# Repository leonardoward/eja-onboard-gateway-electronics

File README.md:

# EJA Onboard Gateway - Electronic Design

EJA Onboard Gateway - Electronic Design - [2020 Hackaday Dream Team Challenge for Conservation X Labs](https://hackaday.io/project/173457-2020-hdp-dream-team-conservation-x-labs)

Onboard Gateway is a 134.11 mm x 62.48 mm PCB that integrates the 3 main components (ESP32, LoRa and USB LiIon/LiPoly charger)

This repository contains the KiCad design for the PCB of the Onboard Gateway. It also contains the 3D models used to visualize the design in the KiCad 3D viewer.

## Main Components ##

Sources:

- [ESP32-DEVKITC-32D](https://www.digikey.com/product-detail/es/espressif-systems/ESP32-DEVKITC-32D/1965-1000-ND/9356990)
- [RFM95W LoRa Radio](https://www.digikey.com/product-detail/es/adafruit-industries-llc/3072/1528-1667-ND/6005357)
- [USB LiIon/LiPoly charger](https://www.adafruit.com/product/259)

## Schematic ##

[For a detailed explanation of the schematic visit the following log.](https://hackaday.io/project/173457/log/181839-onboard-gateway-v10-schematic-and-pcb-design)

## PCB Layout ##

## Assembly ##

Components List:

1. [TERM BLK 2P SIDE ENT 5.08MM PCB](https://www.digikey.com/product-detail/es/on-shore-technology-inc/OSTTC022162/ED2609-ND/614558)
2. [CONN HEADER R/A 2POS 2.5MM](https://www.digikey.com/product-detail/es/jst-sales-america-inc/S2B-XH-A-1-LF-SN/455-4226-ND/9961922)
3. [CONN HEADER VERT 2POS 2.54MM](https://www.digikey.com/product-detail/es/3m/2340-6111TG/3M11928-ND/1237275)
4. [CONN HEADER VERT 2POS 2.54MM](https://www.digikey.com/product-detail/es/3m/2340-6111TG/3M11928-ND/1237275)
5. [CONN HDR 6POS 0.1 TIN PCB](https://www.digikey.com/product-detail/es/sullins-connector-solutions/PPTC061LFBN-RC/S7004-ND/810145)
6. 2POS JST cable (included in the [USB LiIon/LiPoly charger](https://www.adafruit.com/product/259))
7. [USB LiIon/LiPoly charger](https://www.adafruit.com/product/259)
8. Onboard Gateway V1.0
9. [CONN HEADER VERT 2POS 2.54MM](https://www.digikey.com/product-detail/es/3m/2340-6111TG/3M11928-ND/1237275)
10. [RES 249 OHM 1/4W 1% AXIAL](https://www.digikey.com/product-detail/en/stackpole-electronics-inc/RNF14FTD249R/RNF14FTD249RCT-ND/1974990)
11. [RES 249 OHM 1/4W 1% AXIAL](https://www.digikey.com/product-detail/en/stackpole-electronics-inc/RNF14FTD249R/RNF14FTD249RCT-ND/1974990)
12. [TERM BLK 2P SIDE ENT 5.08MM PCB](https://www.digikey.com/product-detail/es/on-shore-technology-inc/OSTTC022162/ED2609-ND/614558)
13. [CONN HEADER VERT 6POS 2.54MM](https://www.digikey.com/product-detail/es/3m/2340-6111TG/3M11928-ND/1237275)
14. [CONN HDR 2POS 0.1 GOLD PCB](https://www.digikey.com/product-detail/es/sullins-connector-solutions/PPPC021LFBN-RC/S7035-ND/810174)
15. [CONN HEADER VERT 3POS 2.54MM](https://www.digikey.com/product-detail/es/3m/2340-6111TG/3M11928-ND/1237275)
16. [CONN JUMPER SHORTING .100" GOLD](https://www.digikey.com/product-detail/es/sullins-connector-solutions/QPC02SXGN-RC/S9337-ND/2618262)
17. [CONN HDR 19POS 0.1 TIN PCB](https://www.digikey.com/product-detail/es/sullins-connector-solutions/PPTC191LFBN-RC/S7017-ND/810157)
18. [ESP32-DEVKITC-32D](https://www.digikey.com/product-detail/es/espressif-systems/ESP32-DEVKITC-32D/1965-1000-ND/9356990)
19. [CONN HDR 19POS 0.1 TIN PCB](https://www.digikey.com/product-detail/es/sullins-connector-solutions/PPTC191LFBN-RC/S7017-ND/810157)
20. [CONN HDR 16POS 0.1 TIN PCB](https://www.digikey.com/product-detail/es/sullins-connector-solutions/PPTC161LFBN-RC/S7014-ND/810154)
21. [CONN HDR 12POS 0.1 TIN PCB](https://www.digikey.com/product-detail/es/sullins-connector-solutions/PPTC121LFBN-RC/S6100-ND/807231) (I used 2 [CONN HDR 6POS 0.1 TIN PCB](https://www.digikey.com/product-detail/es/sullins-connector-solutions/PPTC061LFBN-RC/S7004-ND/810145) in the image)
22. [CONN HDR 9POS 0.1 GOLD PCB](https://www.digikey.com/product-detail/es/sullins-connector-solutions/PPPC091LFBN-RC/S7042-ND/810181)
23. [CONN HEADER VERT 2POS 2.54MM](https://www.digikey.com/product-detail/es/3m/2340-6111TG/3M11928-ND/1237275)
24. [CONN HEADER VERT 2POS 2.54MM](https://www.digikey.com/product-detail/es/3m/2340-6111TG/3M11928-ND/1237275)
25. [CONN HEADER VERT 2POS 2.54MM](https://www.digikey.com/product-detail/es/3m/2340-6111TG/3M11928-ND/1237275)
26. [CONN HEADER VERT 2POS 2.54MM](https://www.digikey.com/product-detail/es/3m/2340-6111TG/3M11928-ND/1237275)
27. [RES 100 OHM 3W 5% AXIAL](https://www.digikey.com/product-detail/en/vishay-beyschlag-draloric-bc-components/AC03000001000JAC00/PPC3W100CT-ND/596604)
28. [RES 100 OHM 3W 5% AXIAL](https://www.digikey.com/product-detail/en/vishay-beyschlag-draloric-bc-components/AC03000001000JAC00/PPC3W100CT-ND/596604)
29. [RES 100 OHM 3W 5% AXIAL](https://www.digikey.com/product-detail/en/vishay-beyschlag-draloric-bc-components/AC03000001000JAC00/PPC3W100CT-ND/596604)
30. [RES 100 OHM 3W 5% AXIAL](https://www.digikey.com/product-detail/en/vishay-beyschlag-draloric-bc-components/AC03000001000JAC00/PPC3W100CT-ND/596604)
31. [CONN HDR 5POS 0.1 GOLD PCB](https://www.digikey.com/product-detail/es/sullins-connector-solutions/PPTC051LFBN-RC/S6103-ND/807239)
32. [RFM95W LoRa Radio](https://www.digikey.com/product-detail/es/adafruit-industries-llc/3072/1528-1667-ND/6005357)
33. CONN HEADER VERT 16POS 2.54MM (included in [RFM95W LoRa Radio](https://www.digikey.com/product-detail/es/adafruit-industries-llc/3072/1528-1667-ND/6005357))

[For a detailed Bill of Materials visit the following log.](https://hackaday.io/project/173457/log/183759-onboard-gateway-v10-bill-of-materials)

[For a detailed explanation about the soldering and assembly procedure visit the following log.](https://hackaday.io/project/173457/log/183665-onboard-gateway-v10-assembly)

## Wiring Diagrams ##

The following diagram presents the physical connections of the different boards and components of the Onboard Gateway, that includes:

- 3.7V 1 Cell Battery
- Leds (Charge, Done and 4 Miscellaneous)
- PCB Board for the Onboard Gateway V1.0
- 5V Charger (only used to charge the battery)
- Micro USB Breakout Board
- Switch

[For more information about the wiring diagrams and the project visit the following log.](https://hackaday.io/project/173457-2020-hdp-dream-team-conservation-x-labs/log/182586-onboard-gateway-v10-wiring-diagram)

## Future improvements ##

[For more information about the recommended future improvements for the electronic design visit the following log.](https://hackaday.io/project/173457/log/183807-future-improvements-pcb-design)

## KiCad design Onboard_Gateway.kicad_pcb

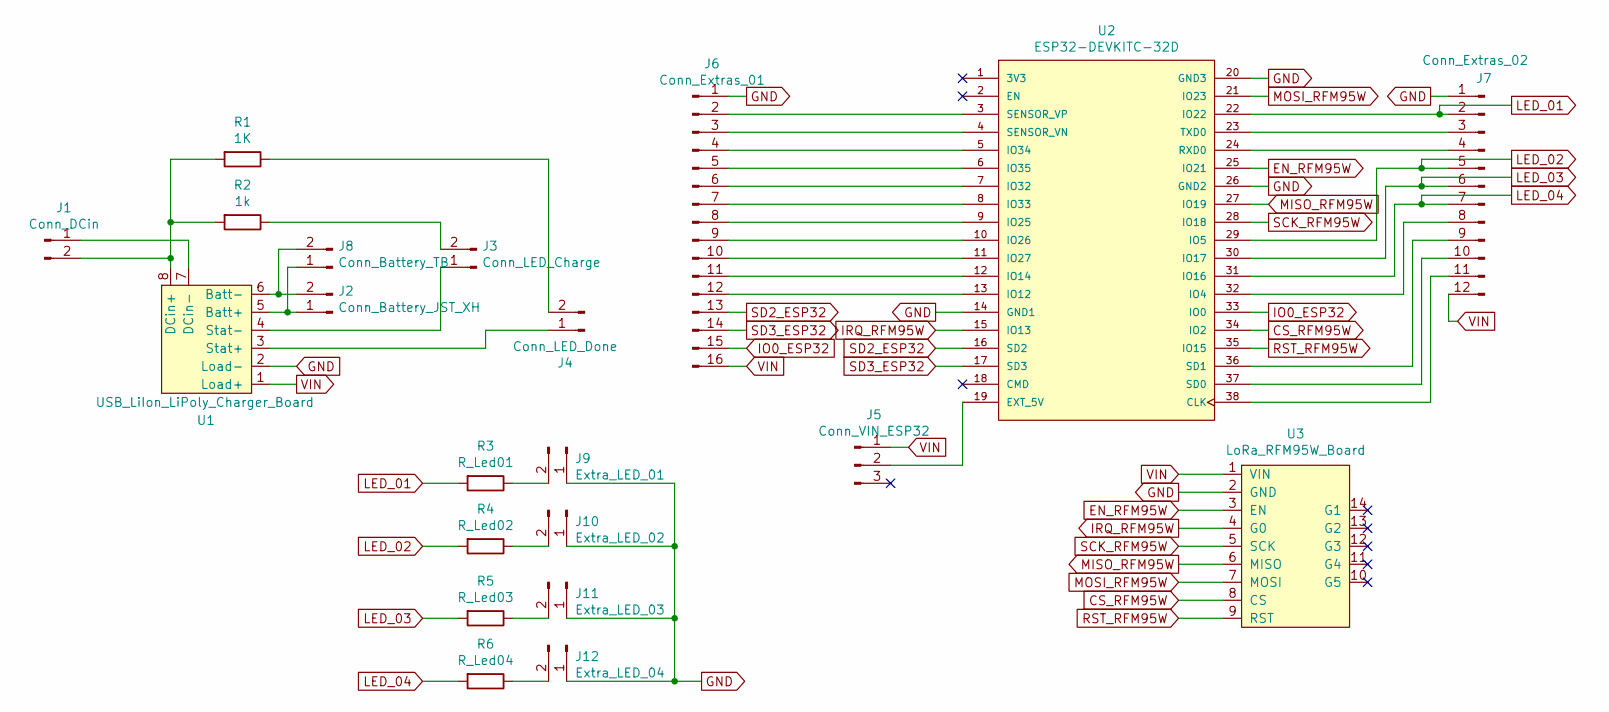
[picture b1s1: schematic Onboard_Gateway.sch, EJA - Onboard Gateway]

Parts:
J1: Conn_DCin; TerminalBlock_bornier-2_P5.08mm
J2: Conn_Battery_JST_XH; JST_XH_S2B-XH-A-1_1x02_P2.50mm_Horizontal
J3: Conn_LED_Charge; PinHeader_1x02_P2.54mm_Vertical
J4: Conn_LED_Done; PinHeader_1x02_P2.54mm_Vertical
J5: Conn_VIN_ESP32; PinHeader_1x03_P2.54mm_Vertical
J6: Conn_Extras_01; PinSocket_1x16_P2.54mm_Vertical
J7: Conn_Extras_02; PinSocket_1x12_P2.54mm_Vertical
J8: Conn_Battery_TB; TerminalBlock_bornier-2_P5.08mm
J9: Extra_LED_01; PinHeader_1x02_P2.54mm_Vertical
J10: Extra_LED_02; PinHeader_1x02_P2.54mm_Vertical
J11: Extra_LED_03; PinHeader_1x02_P2.54mm_Vertical
J12: Extra_LED_04; PinHeader_1x02_P2.54mm_Vertical
R1: 1K; R_Axial_DIN0207_L6.3mm_D2.5mm_P10.16mm_Horizontal
R2: 1k; R_Axial_DIN0207_L6.3mm_D2.5mm_P10.16mm_Horizontal
R3: R_Led01; R_Axial_DIN0207_L6.3mm_D2.5mm_P10.16mm_Horizontal
R4: R_Led02; R_Axial_DIN0207_L6.3mm_D2.5mm_P10.16mm_Horizontal
R5: R_Led03; R_Axial_DIN0207_L6.3mm_D2.5mm_P10.16mm_Horizontal
R6: R_Led04; R_Axial_DIN0207_L6.3mm_D2.5mm_P10.16mm_Horizontal
U1: USB_LiIon_LiPoly_Charger_Board
U2: ESP32-DEVKITC-32D; MODULE_ESP32-DEVKITC-32D
U3: LoRa_RFM95W_Board; RFM95W-Board

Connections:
CS_RFM95W: U2.34 (IO2), U3.8 (CS)
EN_RFM95W: U2.25 (IO21), U3.3 (EN)
GND: J6.1, J7.1, J9.1, J10.1, J11.1, J12.1, U1.2 (Load-), U2.14 (GND1), U2.20 (GND3), U2.26 (GND2), U3.2 (GND)
IO0_ESP32: J6.15, U2.33 (IO0)
IRQ_RFM95W: U2.15 (IO13), U3.4 (G0)
LED_01: J7.2, R3.2, U2.22 (IO22)
LED_02: J7.5, R4.2, U2.29 (IO5)
LED_03: J7.6, R5.2, U2.30 (IO17)
LED_04: J7.7, R6.2, U2.31 (IO16)
MISO_RFM95W: U2.27 (IO19), U3.6 (MISO)
MOSI_RFM95W: U2.21 (IO23), U3.7 (MOSI)
unnamed: J1.1, U1.7 (DCin-)
unnamed: J1.2, R1.2, R2.2, U1.8 (DCin+)
unnamed: J2.1, J8.1, U1.5 (Batt+)
unnamed: J2.2, J8.2, U1.6 (Batt-)
unnamed: J3.1, U1.4 (Stat-)
unnamed: J3.2, R2.1
unnamed: J4.1, U1.3 (Stat+)
unnamed: J4.2, R1.1
unnamed: J5.2, U2.19 (EXT_5V)
unnamed: J6.2, U2.3 (SENSOR_VP)
unnamed: J6.3, U2.4 (SENSOR_VN)
unnamed: J6.4, U2.5 (IO34)
unnamed: J6.5, U2.6 (IO35)
unnamed: J6.6, U2.7 (IO32)
unnamed: J6.7, U2.8 (IO33)
unnamed: J6.8, U2.9 (IO25)
unnamed: J6.9, U2.10 (IO26)
unnamed: J6.10, U2.11 (IO27)
unnamed: J6.11, U2.12 (IO14)
unnamed: J6.12, U2.13 (IO12)
unnamed: J7.3, U2.23 (TXD0)
unnamed: J7.4, U2.24 (RXD0)
unnamed: J7.8, U2.32 (IO4)
unnamed: J7.9, U2.36 (SD1)
unnamed: J7.10, U2.37 (SD0)
unnamed: J7.11, U2.38 (CLK)
unnamed: J9.2, R3.1
unnamed: J10.2, R4.1
unnamed: J11.2, R5.1
unnamed: J12.2, R6.1
RST_RFM95W: U2.35 (IO15), U3.9 (RST)
SCK_RFM95W: U2.28 (IO18), U3.5 (SCK)
SD2_ESP32: J6.13, U2.16 (SD2)
SD3_ESP32: J6.14, U2.17 (SD3)
VIN: J5.1, J6.16, J7.12, U1.1 (Load+), U3.1 (VIN)

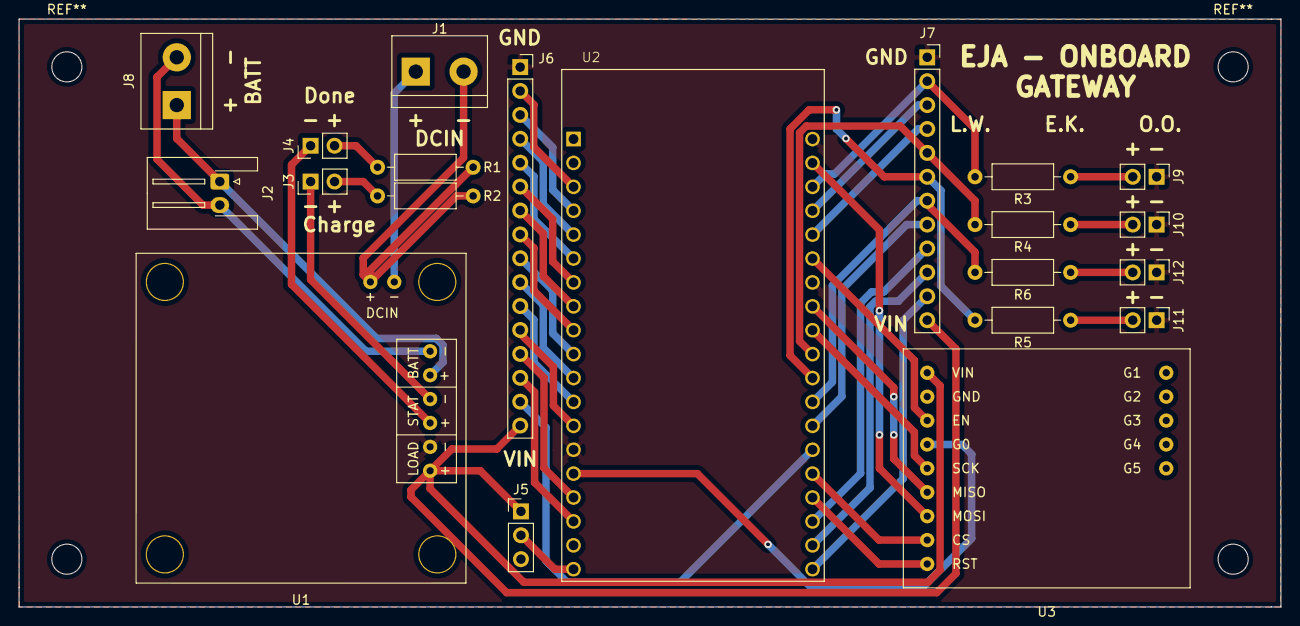
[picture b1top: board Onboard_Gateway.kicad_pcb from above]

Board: 2 copper layers, 134.1 x 62.5 mm, 21 parts (0 on the bottom side), 46 nets.

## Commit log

2020-09-28 Added KiCad design
2020-09-28 Added assembly guide and wiring diagrams
2020-09-28 Added components image
2020-09-28 Added components list
2020-09-28 Added future improvements
